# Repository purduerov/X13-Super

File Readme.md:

# X13-Super-Module

This is an advanced way to manage all the board repos for IEEE ROV. 
Each board's repo is treated as a submodule. 
Git submodules do not track the files inside a submodule, they only point to a commit in the submodule.

### Updating to changes

To get the version pointed at by the super module (this repo), run:  
`git submodule update --init --recursive`  
This can be accessed easier via:  
`git config --global alias.sup 'submodule update --init --recursive'`  
so that you can then type `git sup`

When you cd into a submodule, you will be in a detached HEAD state. You will want to
`git switch` or `git checkout` a branch. To find the branches, run `git branch` or
`git branch -r` to see remote branches.

To get the latest version of each submodule, run:  
`git submodule foreach --recursive git pull`.  
Note: you must be on a branch in order to do this.
Alternatively, running `git submodule update --remote` will pull the latest
commits from the branch tracked in `.gitmodules`, but will finished in a detached head state.

To set up a new submodule, run:  
`git submodule add link.copied.from.github`  
To add tracking the for a branch such as master, use:  
`git submodule add -b master link.copied.from.github`  

### Other: Merging and merge conflicts
Running `git merge --ff-only` or `git pull --ff--only` will prevent git from automatically trying to merge
diverged histories. If you are in a conflict merge commit and want to exit, run `git merge --quit`.  

To merge two branches that have diverged, you have several options. 
1. `git merge -s recursive -X ours` and `git merge -s recursive -X theirs` will attempt to interleave
changes from both files. When conflicts arise, it will prefer local/current (ours) changes in 
`-X ours` and the remote/merging branch (theirs) changes in `-X theirs`.
2. `git merge -s ours` this will "merge" the other branch, but discard all of it's changes.
3. If you have diverged histories and want to delete yours, you can "undo" or "delete" several commits,
then fast-forward merge. It is recommended to first make a "backup" branch (rather than messing with reflog), 
by running `git branch local-backup` (local-backup can be any name). Then run `git reset --hard HEAD~N` where
`N` is the number of commits to undo. The run `git merge branch-name` or `git pull` to fastforward merge the
other branch.

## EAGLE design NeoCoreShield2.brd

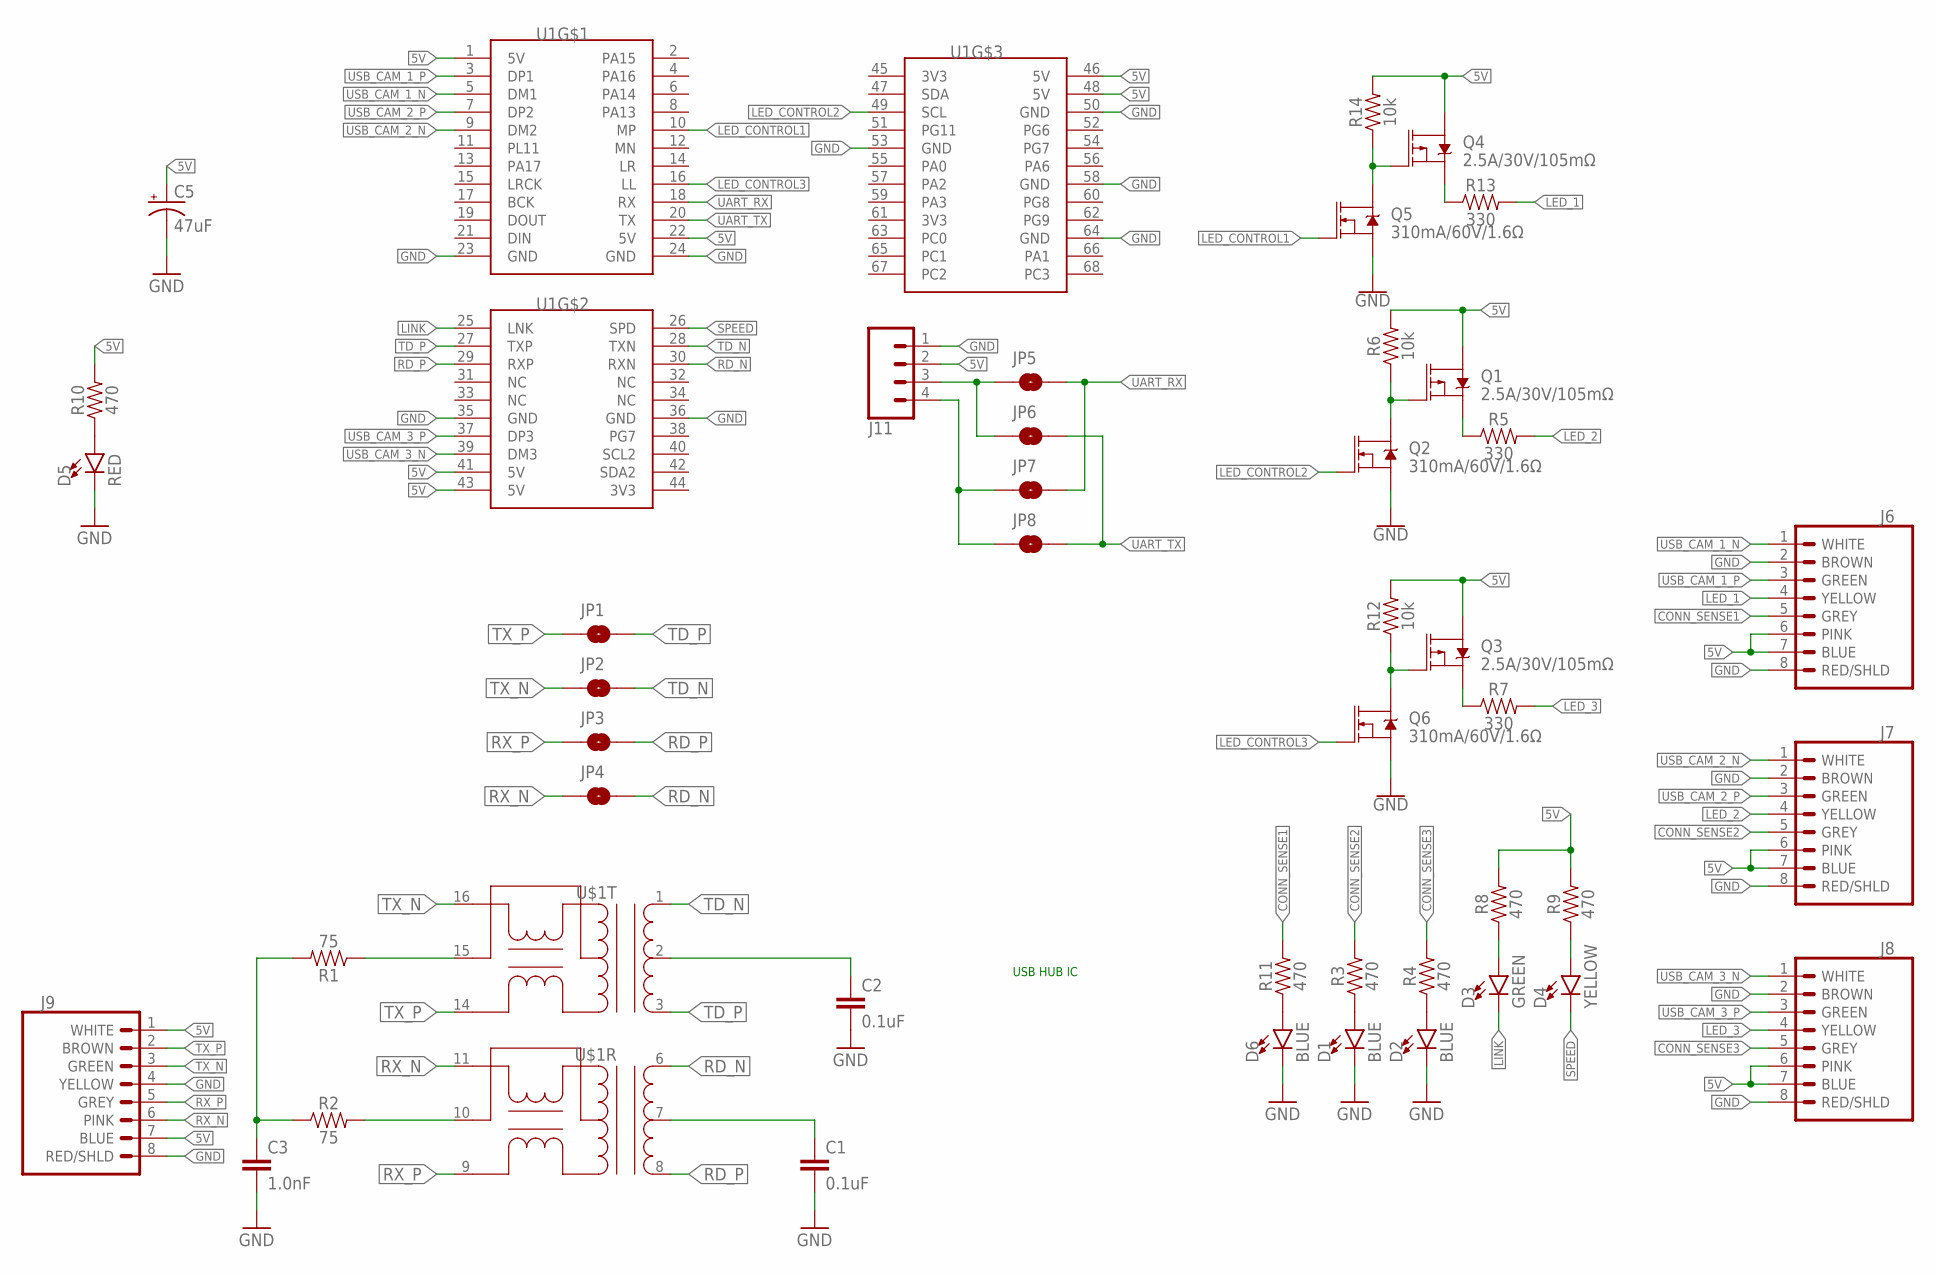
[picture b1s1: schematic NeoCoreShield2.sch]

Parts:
C1, C2: 0.1uF; 0603
C3: 1.0nF; 1206
C5: 47uF; PANASONIC_D
D1, D2, D6: BLUE; 0805
D3: GREEN; 0805
D4: YELLOW; 0805
D5: RED; 0805
J6, J7, J8, J9: BINDER_M12_PAR_8_DIP
J11: CONN_04; 1X04
JP1, JP2, JP3, JP4, JP5, JP6, JP7, JP8: JUMPER-SMT_2_NO_SILK; SMT-JUMPER_2_NO_SILK
Q1, Q3, Q4: 2.5A/30V/105mΩ; SOT23-3
Q2, Q5, Q6: 310mA/60V/1.6Ω; SOT323
R1, R2: 75; 0603
R3, R4, R8, R9, R10, R11: 470; 0603
R5, R7, R13: 330; 0805
R6, R12, R14: 10k; 0603
U1: NANO_PI_NEO_CORE
U$1: ETH-TRANS; SOIC-16-WIDE

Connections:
5V: C5.+, J6.6 (PINK), J6.7 (BLUE), J7.6 (PINK), J7.7 (BLUE), J8.6 (PINK), J8.7 (BLUE), J9.1 (WHITE), J9.7 (BLUE), J11.2, Q1.3 (D), Q3.3 (D), Q4.3 (D), R6.2, R8.2, R9.2, R10.2, R12.2, R14.2, U1.1 (5V), U1.22 (5V), U1.41 (5V), U1.43 (5V), U1.46 (5V), U1.48 (5V)
CONN_SENSE1: J6.5 (GREY), R11.2
CONN_SENSE2: J7.5 (GREY), R3.2
CONN_SENSE3: J8.5 (GREY), R4.2
ETH_TD0_GND: C1.1, U$1.7 (CT)
ETH_TD1_GND: C2.1, U$1.2 (CT)
ETH_TERM_MID: C3.1, R1.2, R2.1
GND: C1.2, C2.2, C3.2, C5.-, D1.C, D2.C, D5.C, D6.C, J6.2 (BROWN), J6.8 (RED/SHLD), J7.2 (BROWN), J7.8 (RED/SHLD), J8.2 (BROWN), J8.8 (RED/SHLD), J9.4 (YELLOW), J9.8 (RED/SHLD), J11.1, Q2.2 (S), Q5.2 (S), Q6.2 (S), U1.23 (GND), U1.24 (GND), U1.35 (GND), U1.36 (GND), U1.50 (GND), U1.53 (GND), U1.58 (GND), U1.64 (GND)
LED_1: J6.4 (YELLOW), R13.2
LED_2: J7.4 (YELLOW), R5.2
LED_3: J8.4 (YELLOW), R7.2
LED_CONTROL1: Q5.1 (G), U1.10 (MP)
LED_CONTROL2: Q2.1 (G), U1.49 (SCL)
LED_CONTROL3: Q6.1 (G), U1.16 (LL)
LINK: D3.C, U1.25 (LNK)
LINK_MID: D3.A, R8.1
unnamed: D1.A, R3.1
unnamed: D2.A, R4.1
unnamed: R2.2, U$1.10 (XCT)
unnamed: D6.A, R11.1
unnamed: Q3.2 (S), R7.1
unnamed: Q3.1 (G), Q6.3 (D), R12.1
unnamed: D5.A, R10.1
unnamed: Q1.2 (S), R5.1
unnamed: Q1.1 (G), Q2.3 (D), R6.1
unnamed: Q4.2 (S), R13.1
unnamed: R1.1, U$1.15 (XCT)
unnamed: Q4.1 (G), Q5.3 (D), R14.1
RD_N: JP4.2, U1.30 (RXN), U$1.6 (D+)
RD_P: JP3.2, U1.29 (RXP), U$1.8 (D-)
RX_N: J9.6 (PINK), JP4.1, U$1.11 (X+)
RX_P: J9.5 (GREY), JP3.1, U$1.9 (X-)
SPEED: D4.C, U1.26 (SPD)
SPEED_MID: D4.A, R9.1
TD_N: JP2.2, U1.28 (TXN), U$1.1 (D+)
TD_P: JP1.2, U1.27 (TXP), U$1.3 (D-)
TX_N: J9.3 (GREEN), JP2.1, U$1.16 (X+)
TX_P: J9.2 (BROWN), JP1.1, U$1.14 (X-)
UART_RX: JP5.2, JP7.2, U1.18 (RX)
UART_RX_TX: J11.3, JP5.1, JP6.1
UART_TX: JP6.2, JP8.2, U1.20 (TX)
UART_TX_RX: J11.4, JP7.1, JP8.1
USB_CAM_1_N: J6.1 (WHITE), U1.5 (DM1)
USB_CAM_1_P: J6.3 (GREEN), U1.3 (DP1)
USB_CAM_2_N: J7.1 (WHITE), U1.9 (DM2)
USB_CAM_2_P: J7.3 (GREEN), U1.7 (DP2)
USB_CAM_3_N: J8.1 (WHITE), U1.39 (DM3)
USB_CAM_3_P: J8.3 (GREEN), U1.37 (DP3)

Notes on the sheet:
USB HUB IC

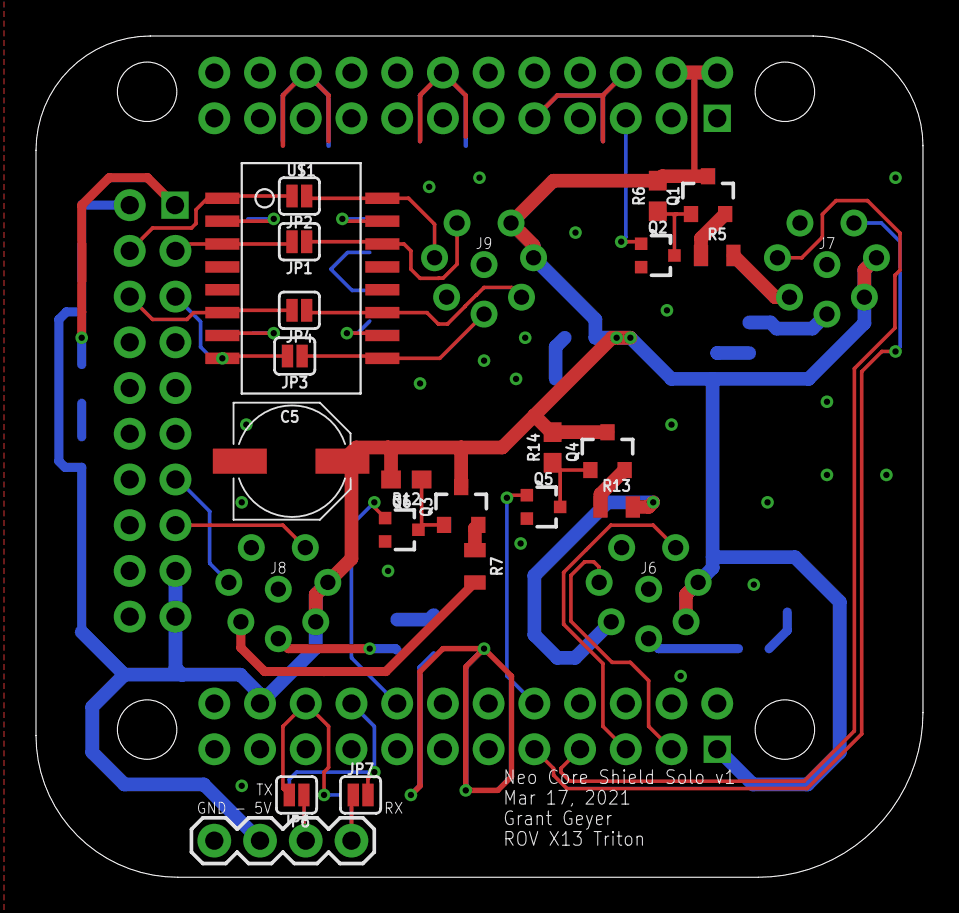
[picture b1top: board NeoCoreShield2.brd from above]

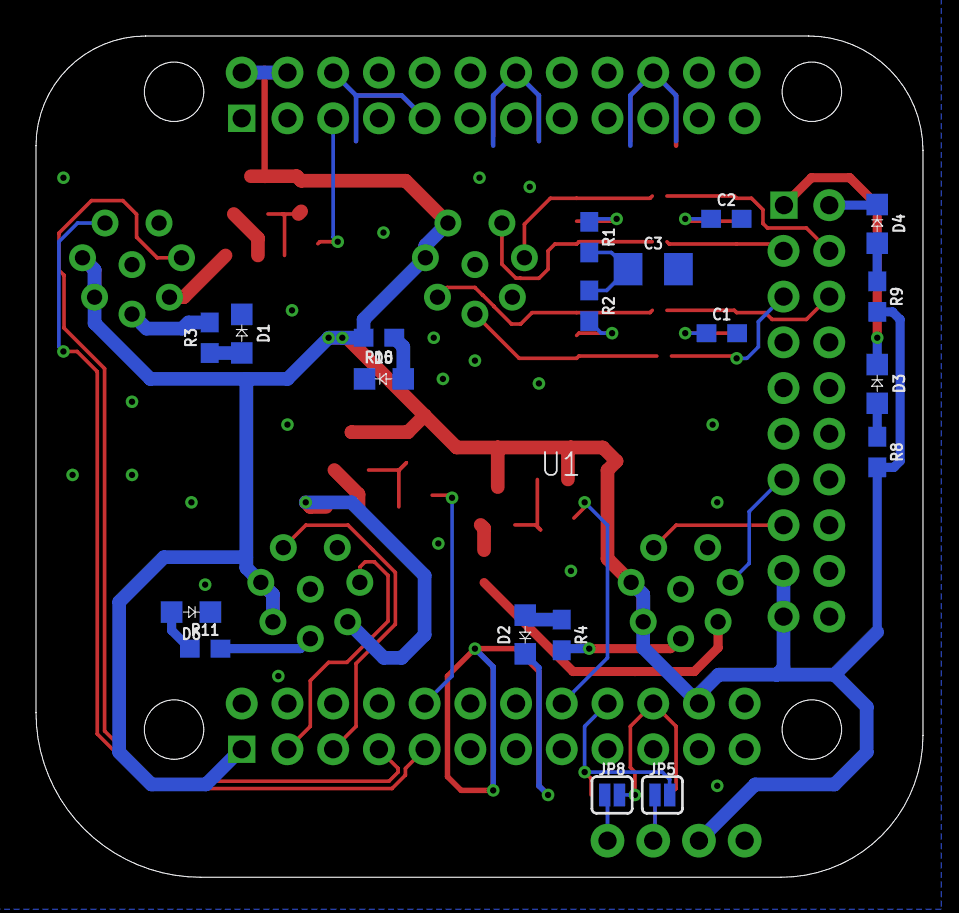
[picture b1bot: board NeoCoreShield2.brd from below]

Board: 2 copper layers, 49.3 x 46.7 mm, 45 parts (20 on the bottom side), 48 nets.

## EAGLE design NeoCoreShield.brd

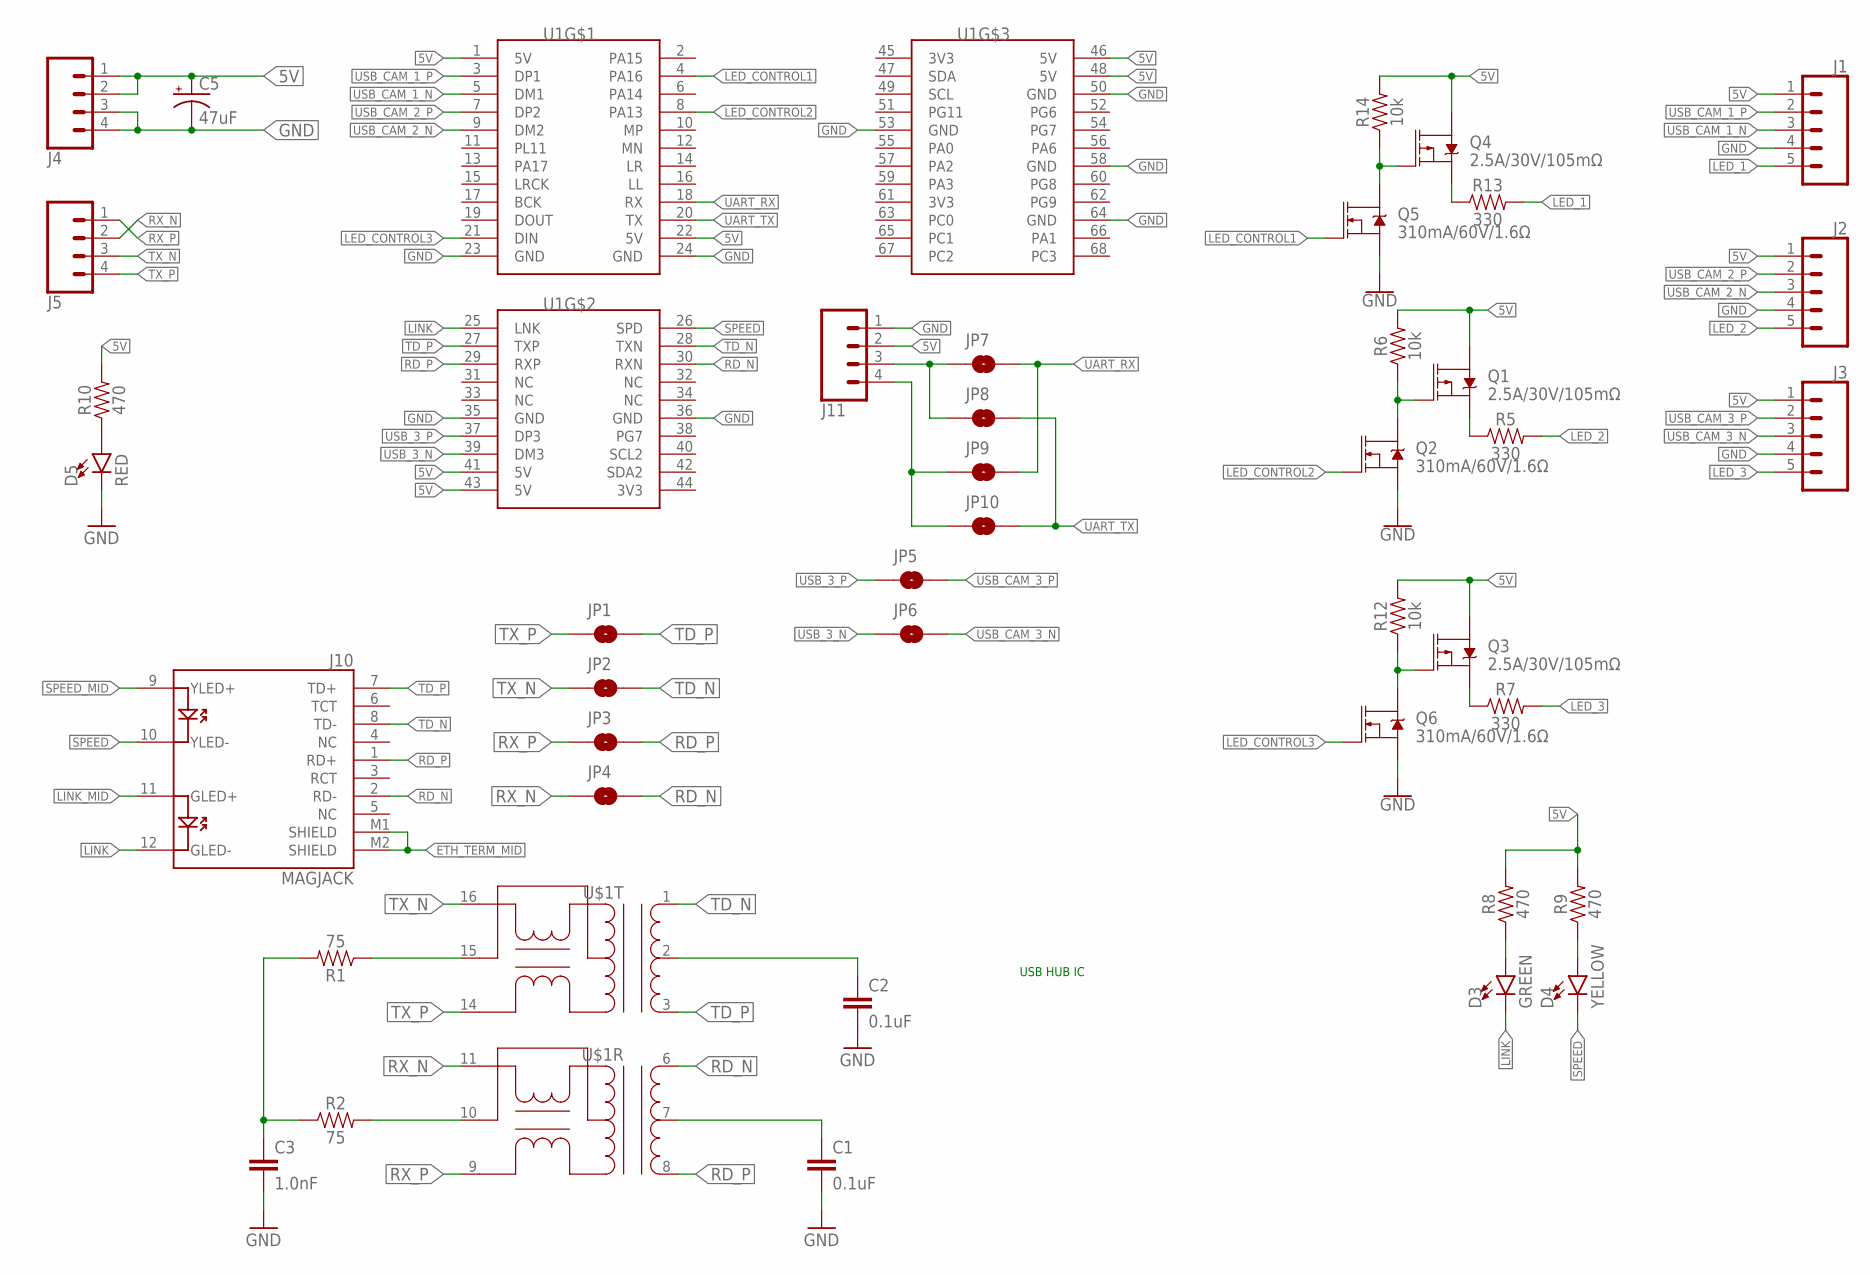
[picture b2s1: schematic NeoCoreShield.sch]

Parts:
C1, C2: 0.1uF; 0603
C3: 1.0nF; 1206
C5: 47uF; PANASONIC_D
D3: GREEN; 0805
D4: YELLOW; 0805
D5: RED; 0805
J1, J2, J3: PXC-PTSM-05-RA
J4, J5: PXC-PTSM-04-RA-1778641
J10: MAGJACK
J11: CONN_04; 1X04
JP1, JP2, JP3, JP4, JP5, JP6, JP7, JP8, JP9, JP10: JUMPER-SMT_2_NO_SILK; SMT-JUMPER_2_NO_SILK
Q1, Q3, Q4: 2.5A/30V/105mΩ; SOT23-3
Q2, Q5, Q6: 310mA/60V/1.6Ω; SOT323
R1, R2: 75; 0603
R5, R7, R13: 330; 0805
R6, R12, R14: 10k; 0603
R8, R9, R10: 470; 0603
U1: NANO_PI_NEO_CORE
U$1: ETH-TRANS; SOIC-16-WIDE

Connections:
5V: C5.+, J1.1, J2.1, J3.1, J4.1, J4.2, J11.2, Q1.3 (D), Q3.3 (D), Q4.3 (D), R6.2, R8.2, R9.2, R10.2, R12.2, R14.2, U1.1 (5V), U1.22 (5V), U1.41 (5V), U1.43 (5V), U1.46 (5V), U1.48 (5V)
ETH_TD0_GND: C1.1, U$1.7 (CT)
ETH_TD1_GND: C2.1, U$1.2 (CT)
ETH_TERM_MID: C3.1, J10.M1 (SHIELD), J10.M2 (SHIELD), R1.2, R2.1
GND: C1.2, C2.2, C3.2, C5.-, D5.C, J1.4, J2.4, J3.4, J4.3, J4.4, J11.1, Q2.2 (S), Q5.2 (S), Q6.2 (S), U1.23 (GND), U1.24 (GND), U1.35 (GND), U1.36 (GND), U1.50 (GND), U1.53 (GND), U1.58 (GND), U1.64 (GND)
LED_1: J1.5, R13.2
LED_2: J2.5, R5.2
LED_3: J3.5, R7.2
LED_CONTROL1: Q5.1 (G), U1.4 (PA16)
LED_CONTROL2: Q2.1 (G), U1.8 (PA13)
LED_CONTROL3: Q6.1 (G), U1.21 (DIN)
LINK: D3.C, J10.12 (GLED-), U1.25 (LNK)
LINK_MID: D3.A, J10.11 (GLED+), R8.1
unnamed: R2.2, U$1.10 (XCT)
unnamed: Q3.2 (S), R7.1
unnamed: Q3.1 (G), Q6.3 (D), R12.1
unnamed: D5.A, R10.1
unnamed: Q1.2 (S), R5.1
unnamed: Q1.1 (G), Q2.3 (D), R6.1
unnamed: Q4.2 (S), R13.1
unnamed: R1.1, U$1.15 (XCT)
unnamed: Q4.1 (G), Q5.3 (D), R14.1
RD_N: J10.2 (RD-), JP4.2, U1.30 (RXN), U$1.6 (D+)
RD_P: J10.1 (RD+), JP3.2, U1.29 (RXP), U$1.8 (D-)
RX_N: J5.2, JP4.1, U$1.11 (X+)
RX_P: J5.1, JP3.1, U$1.9 (X-)
SPEED: D4.C, J10.10 (YLED-), U1.26 (SPD)
SPEED_MID: D4.A, J10.9 (YLED+), R9.1
TD_N: J10.8 (TD-), JP2.2, U1.28 (TXN), U$1.1 (D+)
TD_P: J10.7 (TD+), JP1.2, U1.27 (TXP), U$1.3 (D-)
TX_N: J5.3, JP2.1, U$1.16 (X+)
TX_P: J5.4, JP1.1, U$1.14 (X-)
UART_RX: JP7.2, JP9.2, U1.18 (RX)
UART_RX_TX: J11.3, JP7.1, JP8.1
UART_TX: JP8.2, JP10.2, U1.20 (TX)
UART_TX_RX: J11.4, JP9.1, JP10.1
USB_3_N: JP6.1, U1.39 (DM3)
USB_3_P: JP5.1, U1.37 (DP3)
USB_CAM_1_N: J1.3, U1.5 (DM1)
USB_CAM_1_P: J1.2, U1.3 (DP1)
USB_CAM_2_N: J2.3, U1.9 (DM2)
USB_CAM_2_P: J2.2, U1.7 (DP2)
USB_CAM_3_N: J3.3, JP6.2
USB_CAM_3_P: J3.2, JP5.2

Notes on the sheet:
USB HUB IC

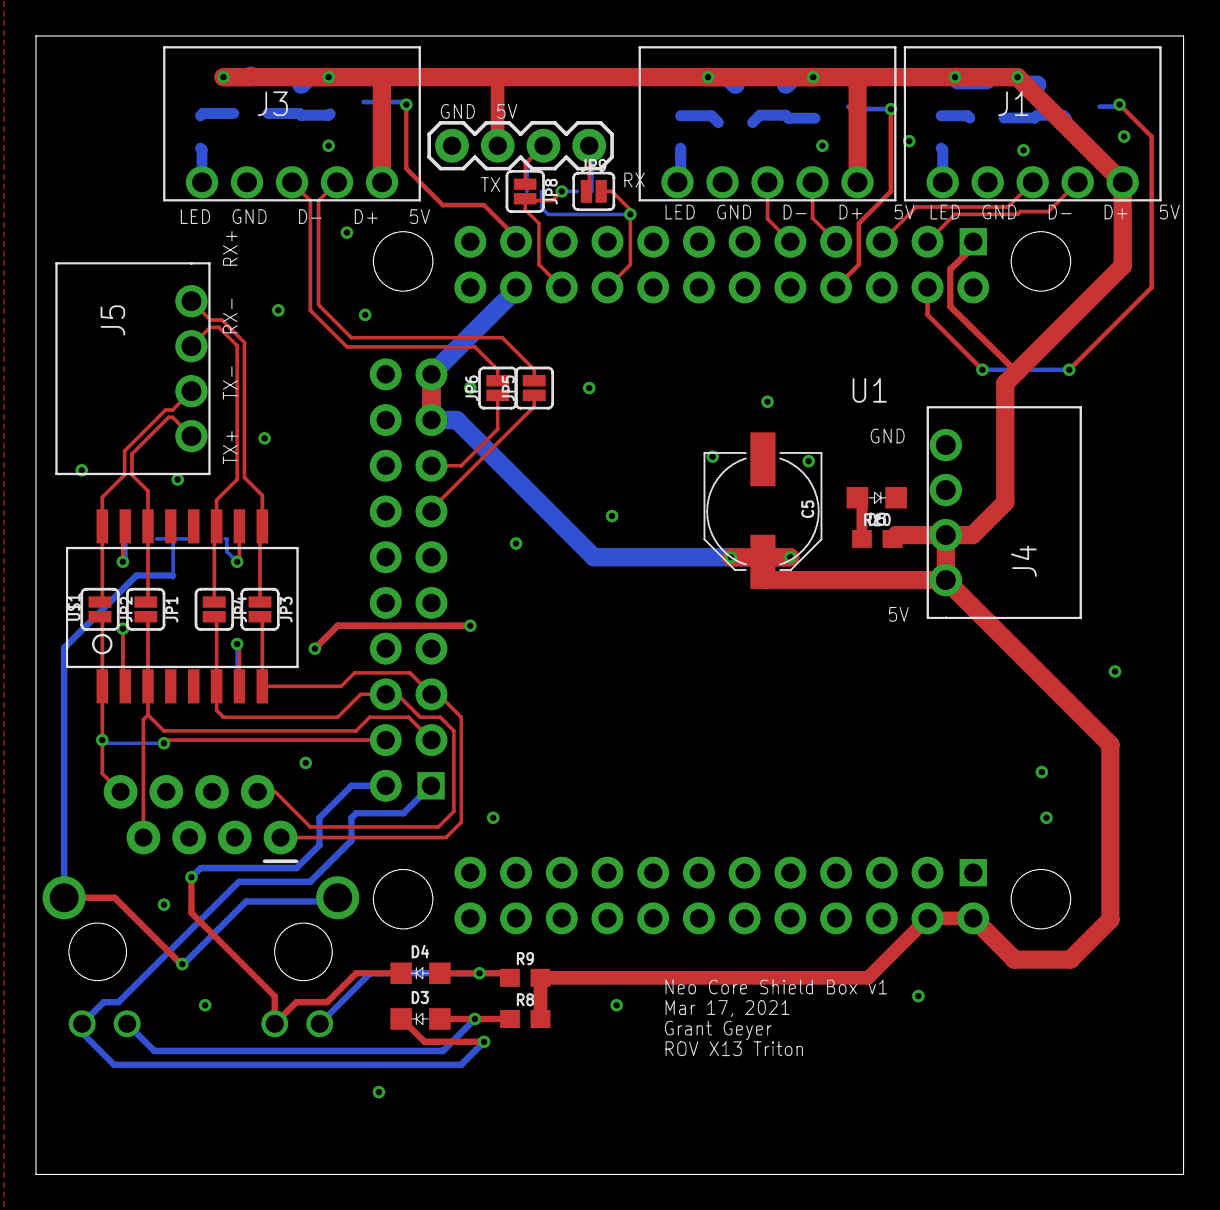
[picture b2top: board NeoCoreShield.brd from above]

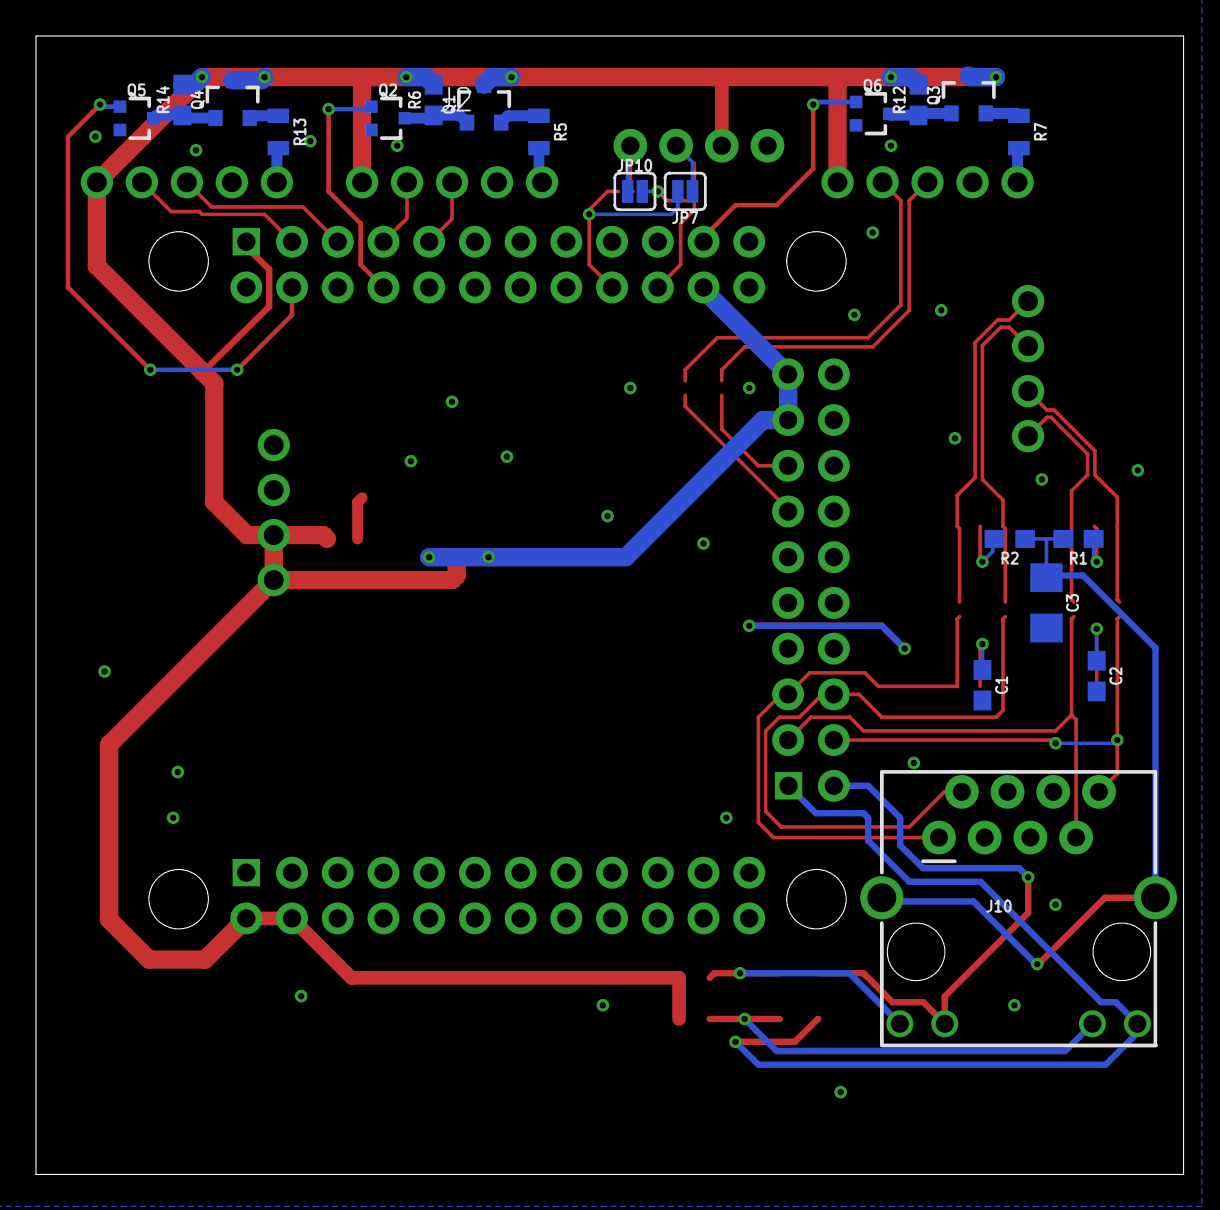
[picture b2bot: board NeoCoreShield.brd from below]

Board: 2 copper layers, 63.8 x 63.2 mm, 43 parts (20 on the bottom side), 44 nets.

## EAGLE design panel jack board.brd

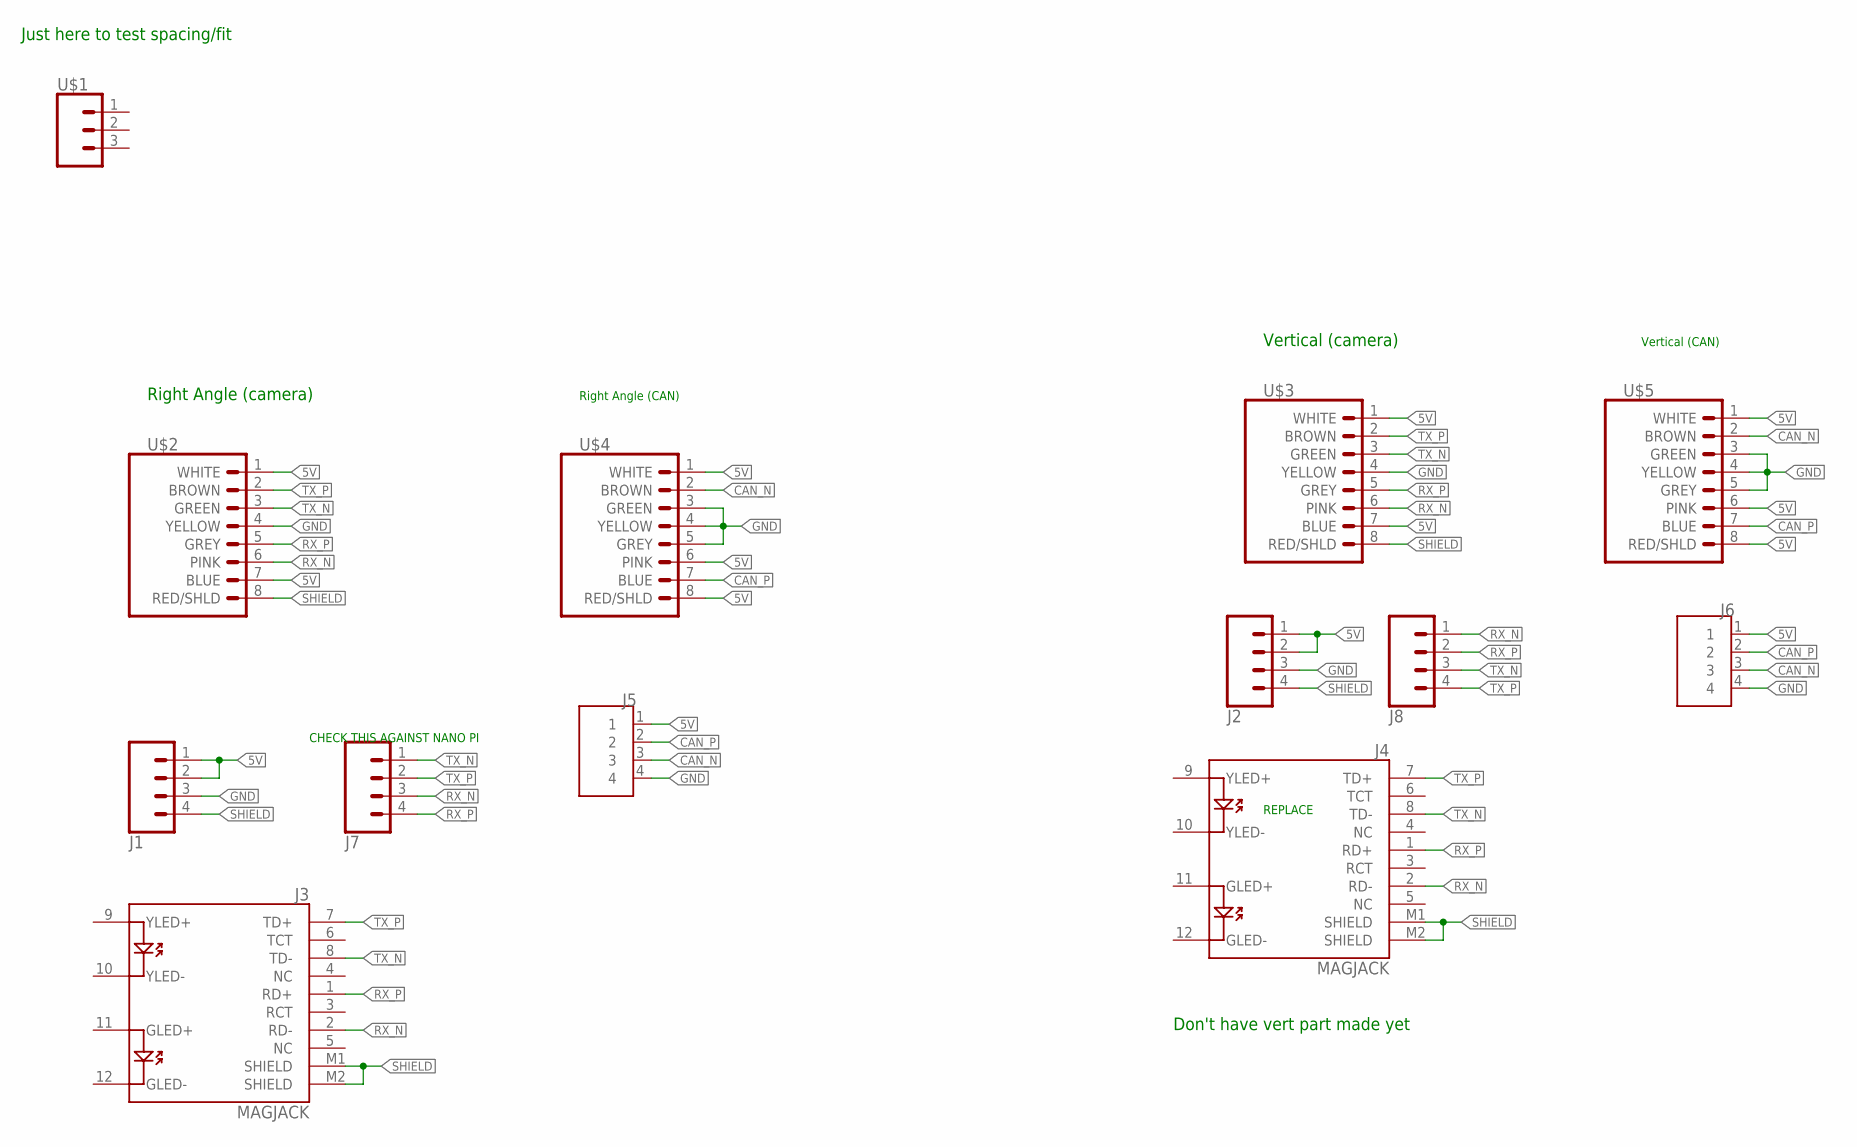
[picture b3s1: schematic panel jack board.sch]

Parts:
J1, J2, J8: PXC-PTSM-04-V-1778573
J3, J4: MAGJACK
J5, J6: 284512-4; TE_284512-4
J7: PXC-PTSM-04-RA-1778641
U$1: BULGIN_BUC4000_3
U$2, U$4: BINDER_M12_RA_8
U$3, U$5: BINDER_M12_PAR_8_DIP

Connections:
5V: J1.1, J1.2, J2.1, J2.2, J5.1, J6.1, U$2.1 (WHITE), U$2.7 (BLUE), U$3.1 (WHITE), U$3.7 (BLUE), U$4.1 (WHITE), U$4.6 (PINK), U$4.8 (RED/SHLD), U$5.1 (WHITE), U$5.6 (PINK), U$5.8 (RED/SHLD)
CAN_N: J5.3, J6.3, U$4.2 (BROWN), U$5.2 (BROWN)
CAN_P: J5.2, J6.2, U$4.7 (BLUE), U$5.7 (BLUE)
GND: J1.3, J2.3, J5.4, J6.4, U$2.4 (YELLOW), U$3.4 (YELLOW), U$4.3 (GREEN), U$4.4 (YELLOW), U$4.5 (GREY), U$5.3 (GREEN), U$5.4 (YELLOW), U$5.5 (GREY)
RX_N: J3.2 (RD-), J4.2 (RD-), J7.3, J8.1, U$2.6 (PINK), U$3.6 (PINK)
RX_P: J3.1 (RD+), J4.1 (RD+), J7.4, J8.2, U$2.5 (GREY), U$3.5 (GREY)
SHIELD: J1.4, J2.4, J3.M1 (SHIELD), J3.M2 (SHIELD), J4.M1 (SHIELD), J4.M2 (SHIELD), U$2.8 (RED/SHLD), U$3.8 (RED/SHLD)
TX_N: J3.8 (TD-), J4.8 (TD-), J7.1, J8.3, U$2.3 (GREEN), U$3.3 (GREEN)
TX_P: J3.7 (TD+), J4.7 (TD+), J7.2, J8.4, U$2.2 (BROWN), U$3.2 (BROWN)

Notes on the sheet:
Just here to test spacing/fit
Right Angle (camera)
Vertical (camera)
Don't have vert part made yet
Right Angle (CAN)
CHECK THIS AGAINST NANO PI
Vertical (CAN)
REPLACE

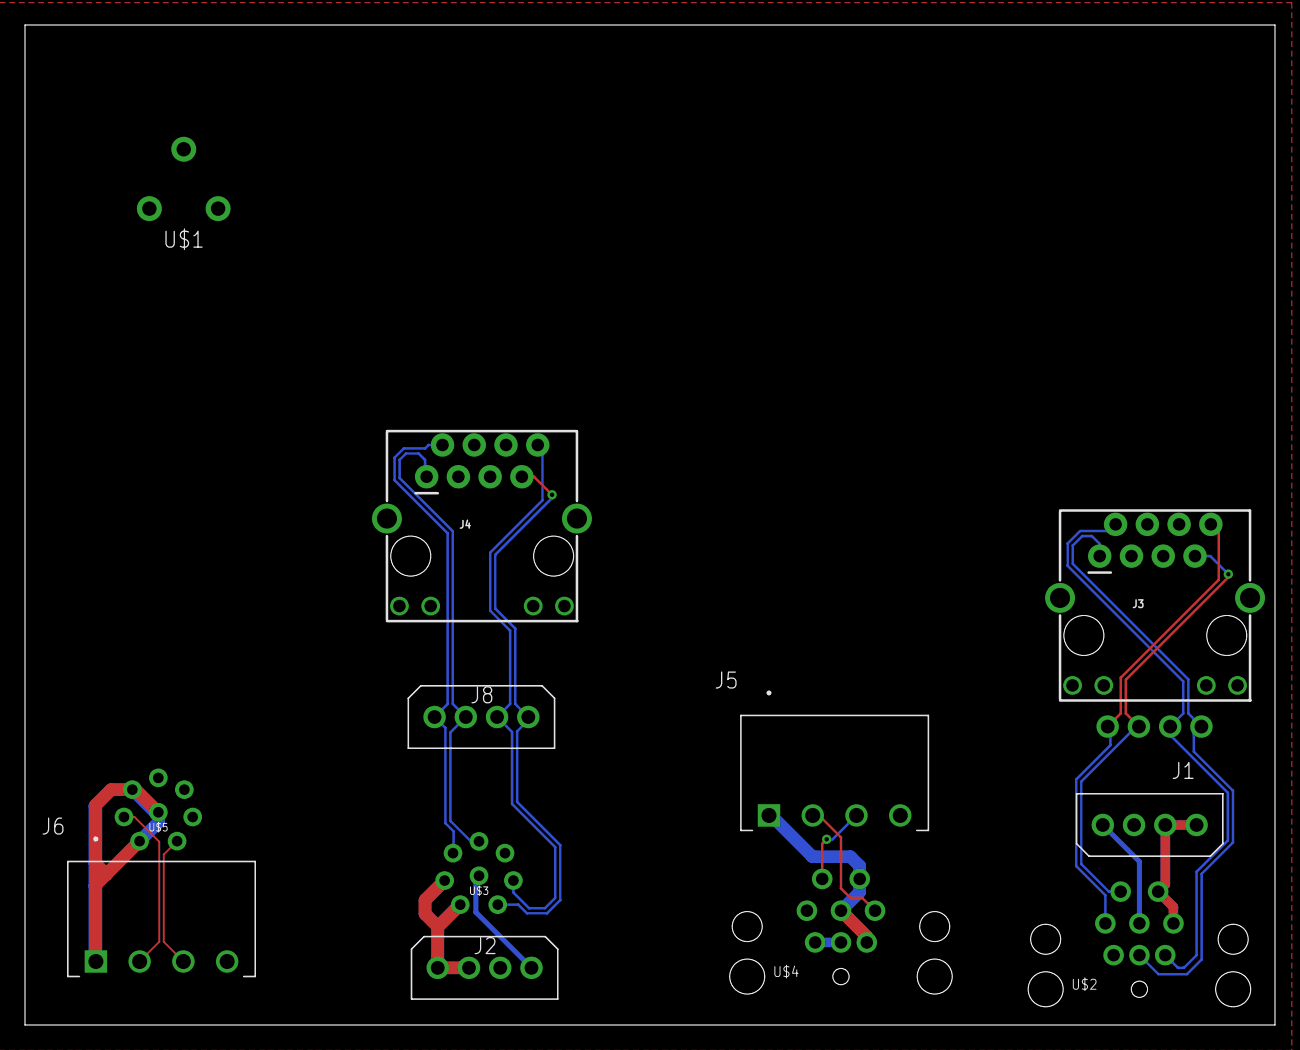
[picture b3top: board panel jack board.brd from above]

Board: 2 copper layers, 100.0 x 80.0 mm, 13 parts (1 on the bottom side), 9 nets.

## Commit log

2020-09-18 setup of super repo
2020-09-19 fix backplane repo url
2020-10-13 rename readme for github viewing
2020-10-25 pull up on all submodules. Grant fixes after design review
2020-11-12 Add Solenoid and custom esc as modules
2020-11-14 fixed broken modules
2020-11-14 actually fixed it this time
2020-12-05 pre design review commits
2021-01-12 First round of PCB orders
2021-03-17 Neo Core Shield and Panel Jack Test Board and Updates a long time coming
2021-03-18 Add panel jack PCB term test board
2021-03-18 Routed Neo Core Shields
2021-03-21 Neo Core Nano Pi Shield order
2021-03-27 Electrical RnD for Sure
2021-03-28 Move Neo Core Shield and Panel Jack Test boards to RnD
2021-04-13 Updates to stuff and April 12 order
2021-05-14 Use SSH URLs
2021-08-12 Closing out the year
2021-08-13 Add Electrical R&D to ssh branch

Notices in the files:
parts and their libraries:
SparkFun-Resistors: Licensing: Creative Commons ShareAlike 4.0 International - https://creativecommons.org/licenses/by-sa/4.0
